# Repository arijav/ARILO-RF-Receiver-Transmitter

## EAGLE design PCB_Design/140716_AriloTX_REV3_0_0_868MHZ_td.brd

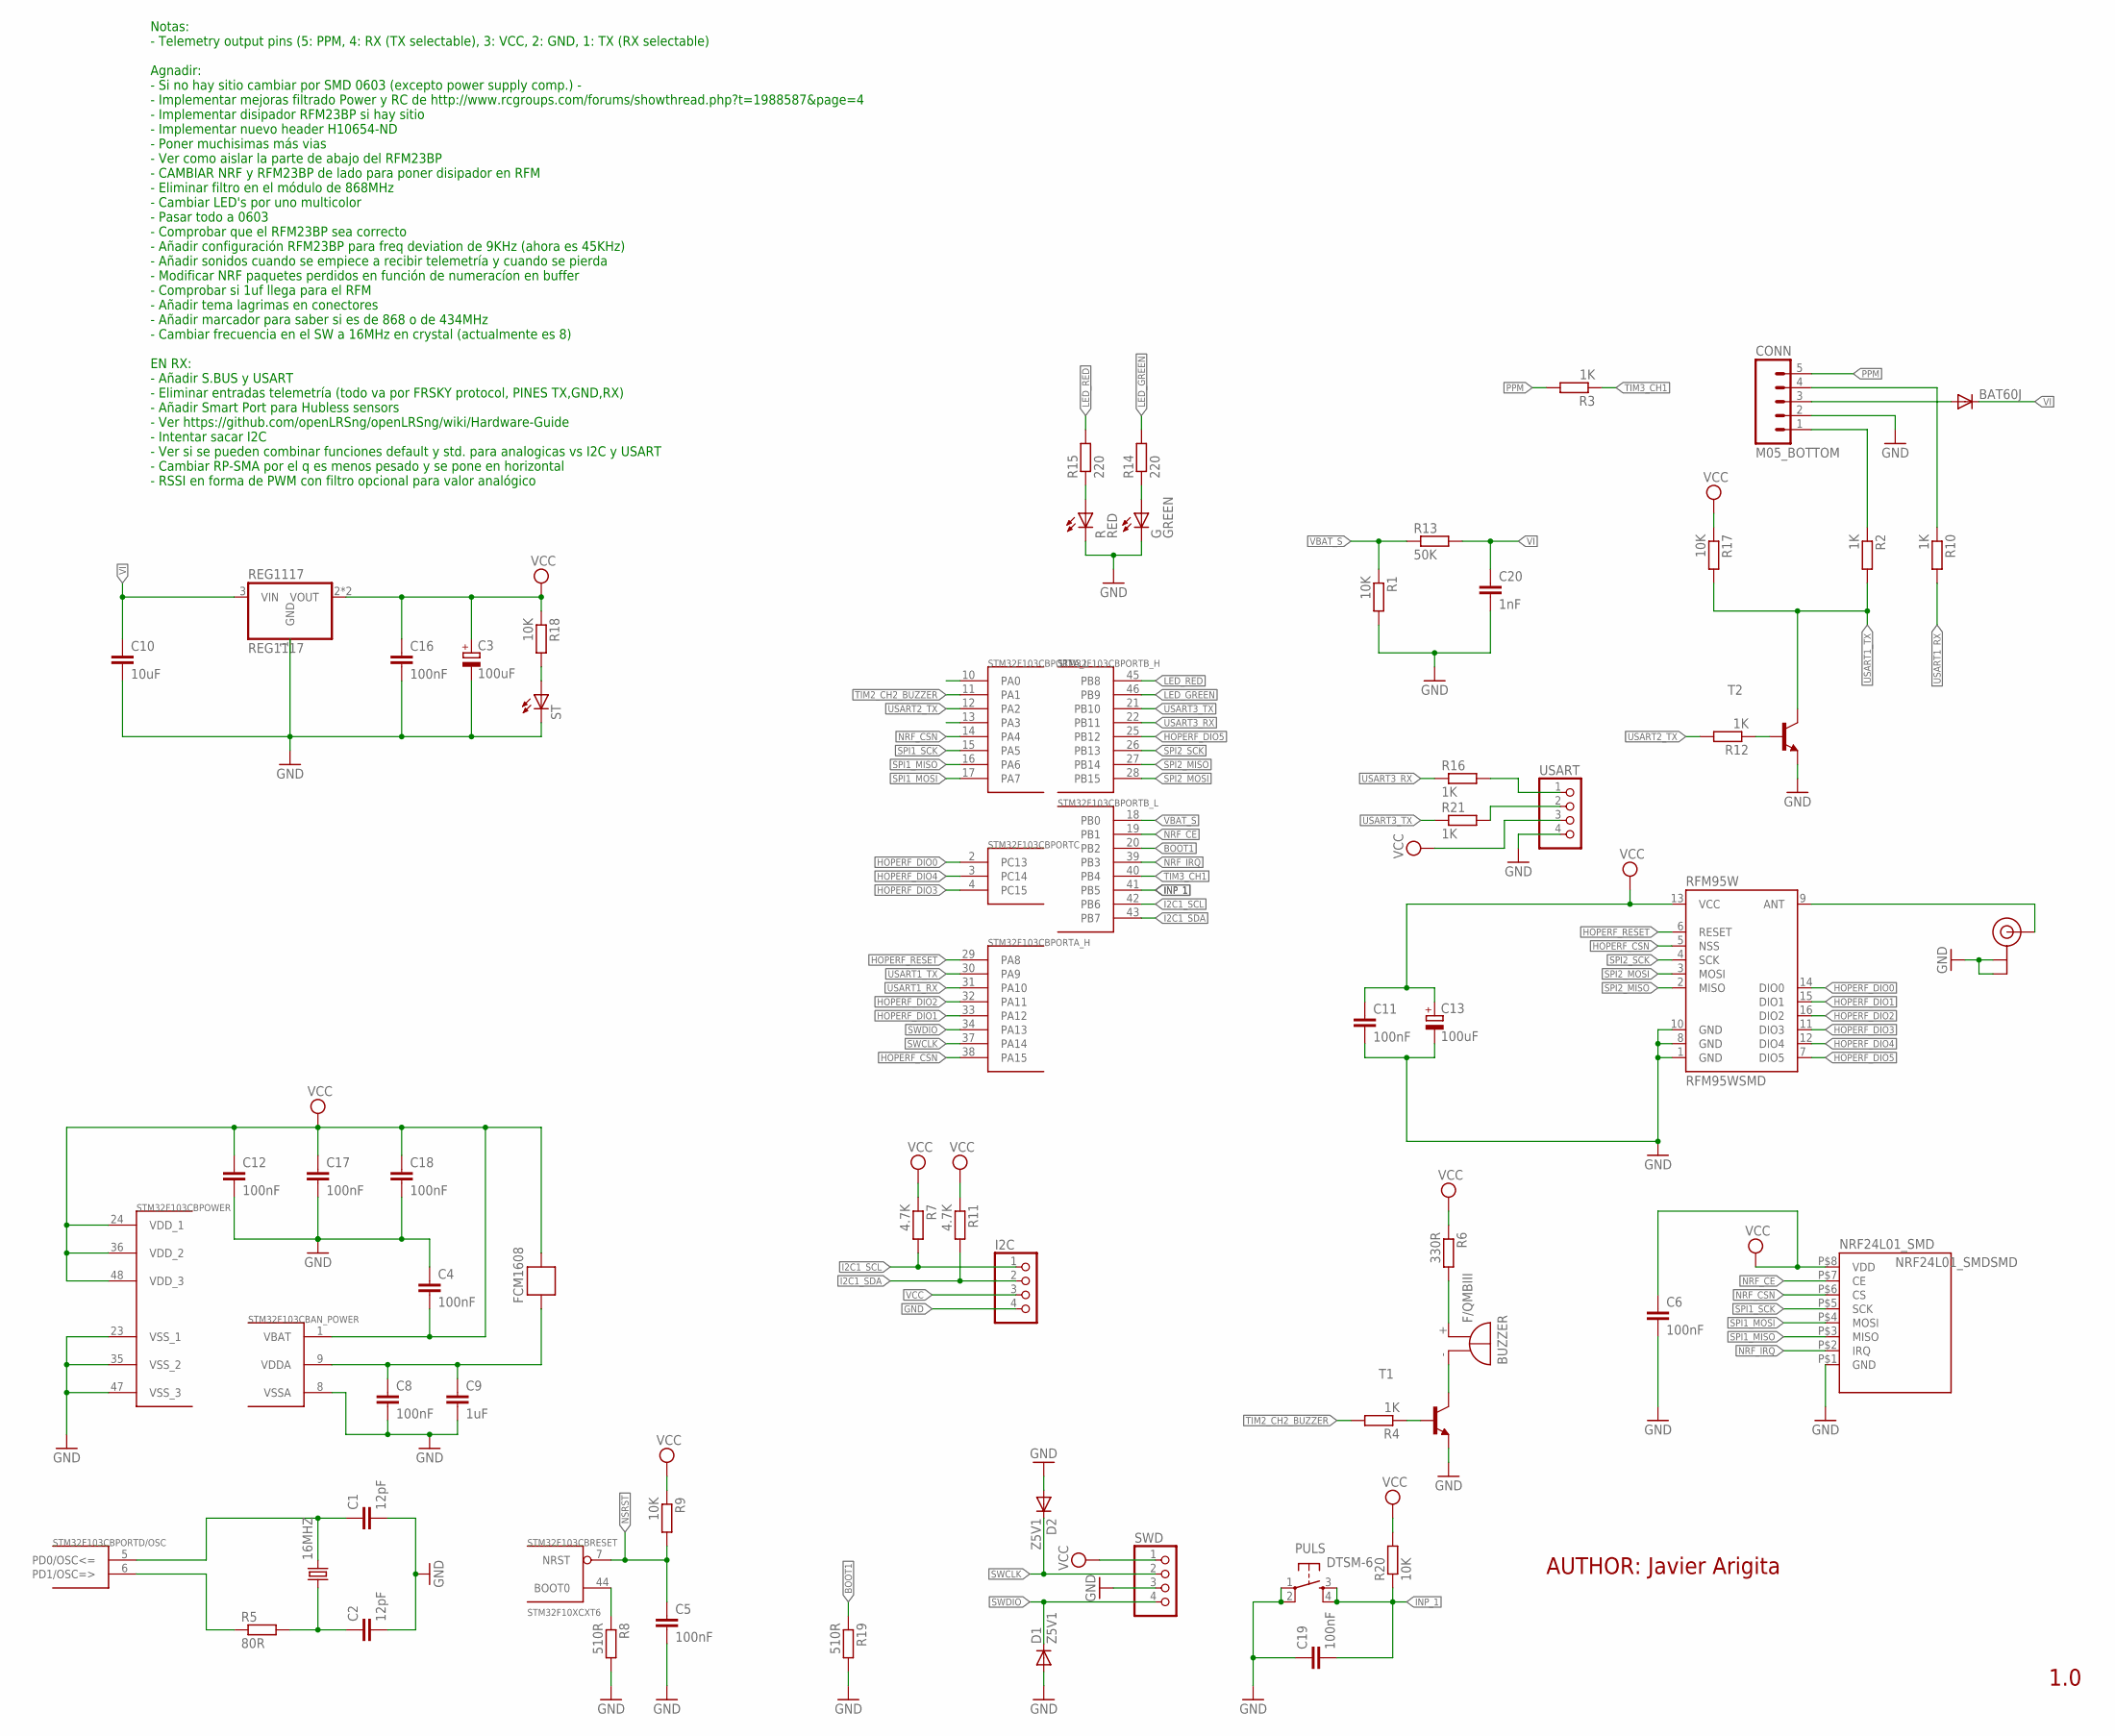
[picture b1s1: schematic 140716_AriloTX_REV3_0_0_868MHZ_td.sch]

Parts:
16MHZ: CRYSTAL5X3; CRYSTAL-SMD-5X3
BAT60J: DIODE-SOD323-R; SOD323-R
BUZZER: F/QMBIII
C1, C2: 12pF; C0603
C3, C13: 100uF; SMC_B
C4, C5, C6, C8, C11, C12, C16, C17, C18, C19: 100nF; C0603
C9: 1uF; C0603
C10: 10uF; C3216
C20: 1nF; C0603
CONN: M05_BOTTOM
D1, D2: Z5V1; SOD323-R
FCM1608: FERRITE-BEAD; R0603
G: GREEN; CHIP-LED0603
I2C: PINHD-1X4; 1X04
NRF24L01_SMD: NRF24L01_SMDSMD; NRF24L01_SMD
PULS: DTSM-6
R: RED; CHIP-LED0603
R1, R9, R17, R18, R20: 10K; R0603
R2, R3, R4, R10, R12, R16, R21: 1K; R0603
R5: 80R; R0603
R6: 330R; R0603
R7, R11: 4.7K; R0603
R8, R19: 510R; R0603
R13: 50K; R0603
R14, R15: 220; R0603
REG1117: REG1117; SOT223
RFM95W: RFM95WSMD; MISIEK_RFM95W_SMD
ST: LEDCHIP-LED0603; CHIP-LED0603
STM32F103CB: STM32F10XCXT6; TQFP48
SWD: PINHD-1X4; 1X04
T1, T2: BC848-NPN-SOT23-BEC; SOT23-BEC
U.FL: U.FL
USART: PINHD-1X4; 1X04

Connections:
BOOT1: R19.1, STM32F103CB.20 (PB2)
GND: C1.2, C2.2, C3.-, C4.1, C5.2, C6.2, C8.2, C9.2, C10.2, C11.2, C12.2, C13.-, C16.2, C17.2, C18.2, C19.1, C20.2, CONN.2, D1.A, D2.A, G.C, I2C.4, NRF24L01_SMD.P$1 (GND), PULS.1, PULS.2, R.C, R1.2, R8.2, R19.2, REG1117.1 (GND), RFM95W.1 (GND), RFM95W.8 (GND), RFM95W.10 (GND), ST.C, STM32F103CB.8 (VSSA), STM32F103CB.23 (VSS_1), STM32F103CB.35 (VSS_2), STM32F103CB.47 (VSS_3), SWD.3, T1.E, T2.E, U.FL.P$1 (GND), U.FL.P$2 (GND), USART.4
HOPERF_CSN: RFM95W.5 (NSS), STM32F103CB.38 (PA15)
HOPERF_DIO0: RFM95W.14 (DIO0), STM32F103CB.2 (PC13)
HOPERF_DIO1: RFM95W.15 (DIO1), STM32F103CB.33 (PA12)
HOPERF_DIO2: RFM95W.16 (DIO2), STM32F103CB.32 (PA11)
HOPERF_DIO3: RFM95W.11 (DIO3), STM32F103CB.4 (PC15)
HOPERF_DIO4: RFM95W.12 (DIO4), STM32F103CB.3 (PC14)
HOPERF_DIO5: RFM95W.7 (DIO5), STM32F103CB.25 (PB12)
HOPERF_RESET: RFM95W.6 (RESET), STM32F103CB.29 (PA8)
I2C1_SCL: I2C.1, R7.2, STM32F103CB.42 (PB6)
I2C1_SDA: I2C.2, R11.2, STM32F103CB.43 (PB7)
INP_1: C19.2, PULS.3, PULS.4, R20.1, STM32F103CB.41 (PB5)
LED_GREEN: R14.2, STM32F103CB.46 (PB9)
LED_RED: R15.2, STM32F103CB.45 (PB8)
unnamed: 16MHZ.3 (2), C1.1, STM32F103CB.5 (PD0/OSC<=)
unnamed: R5.1, STM32F103CB.6 (PD1/OSC=>)
unnamed: 16MHZ.1, C2.1, R5.2
unnamed: R8.1, STM32F103CB.44 (BOOT0)
unnamed: R12.1, T2.B
unnamed: CONN.1, R2.1
unnamed: R.A, R15.1
unnamed: G.A, R14.1
unnamed: CONN.4, R10.1
unnamed: R18.2, ST.A
unnamed: RFM95W.9 (ANT), U.FL.P$3 (SIGNAL)
unnamed: R16.2, USART.1
unnamed: R21.2, USART.2
unnamed: BAT60J.A, CONN.3
unnamed: BUZZER.+ (-), R6.2
unnamed: C8.1, C9.1, FCM1608.2, STM32F103CB.9 (VDDA)
unnamed: R4.1, T1.B
unnamed: BUZZER.- (+), T1.C
NRF_CE: NRF24L01_SMD.P$7 (CE), STM32F103CB.19 (PB1)
NRF_CSN: NRF24L01_SMD.P$6 (CS), STM32F103CB.14 (PA4)
NRF_IRQ: NRF24L01_SMD.P$2 (IRQ), STM32F103CB.39 (PB3)
NSRST: C5.1, R9.2, STM32F103CB.7 (NRST)
PPM: CONN.5, R3.2
SPI1_MISO: NRF24L01_SMD.P$3 (MISO), STM32F103CB.16 (PA6)
SPI1_MOSI: NRF24L01_SMD.P$4 (MOSI), STM32F103CB.17 (PA7)
SPI1_SCK: NRF24L01_SMD.P$5 (SCK), STM32F103CB.15 (PA5)
SPI2_MISO: RFM95W.2 (MISO), STM32F103CB.27 (PB14)
SPI2_MOSI: RFM95W.3 (MOSI), STM32F103CB.28 (PB15)
SPI2_SCK: RFM95W.4 (SCK), STM32F103CB.26 (PB13)
SWCLK: D2.C, STM32F103CB.37 (PA14), SWD.2
SWDIO: D1.C, STM32F103CB.34 (PA13), SWD.4
TIM2_CH2_BUZZER: R4.2, STM32F103CB.11 (PA1)
TIM3_CH1: R3.1, STM32F103CB.40 (PB4)
USART1_RX: R10.2, STM32F103CB.31 (PA10)
USART1_TX: R2.2, R17.2, STM32F103CB.30 (PA9), T2.C
USART2_TX: R12.2, STM32F103CB.12 (PA2)
USART3_RX: R16.1, STM32F103CB.22 (PB11)
USART3_TX: R21.1, STM32F103CB.21 (PB10)
VBAT_S: R1.1, R13.1, STM32F103CB.18 (PB0)
VCC: C3.+, C4.2, C6.1, C11.1, C12.1, C13.+, C16.1, C17.1, C18.1, FCM1608.1, I2C.3, NRF24L01_SMD.P$8 (VDD), R6.1, R7.1, R9.1, R11.1, R17.1, R18.1, R20.2, REG1117.2 (VOUT), REG1117.4 (VOUT), RFM95W.13 (VCC), STM32F103CB.1 (VBAT), STM32F103CB.24 (VDD_1), STM32F103CB.36 (VDD_2), STM32F103CB.48 (VDD_3), SWD.1, USART.3
VI: BAT60J.C, C10.1, C20.1, R13.2, REG1117.3 (VIN)

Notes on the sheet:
AUTHOR: Javier Arigita
1.0
Notas: - Telemetry output pins (5: PPM, 4: RX (TX selectable), 3: VCC, 2: GND, 1: TX (RX selectable) Agnadir: - Si no hay sitio cambiar por SMD 0603 (excepto power supply comp.) - - Implementar mejoras filtrado Power y RC de http://www.rcgroups.com/forums/showthread.php?t=1988587&page=4 - Implement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

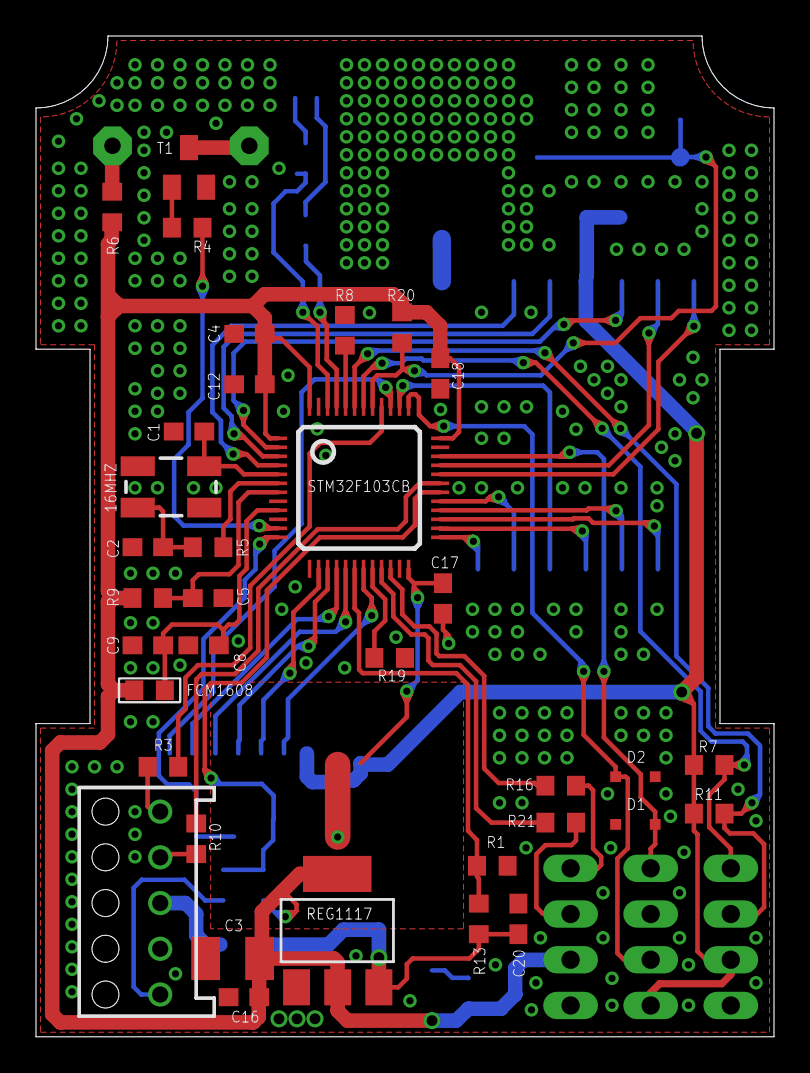
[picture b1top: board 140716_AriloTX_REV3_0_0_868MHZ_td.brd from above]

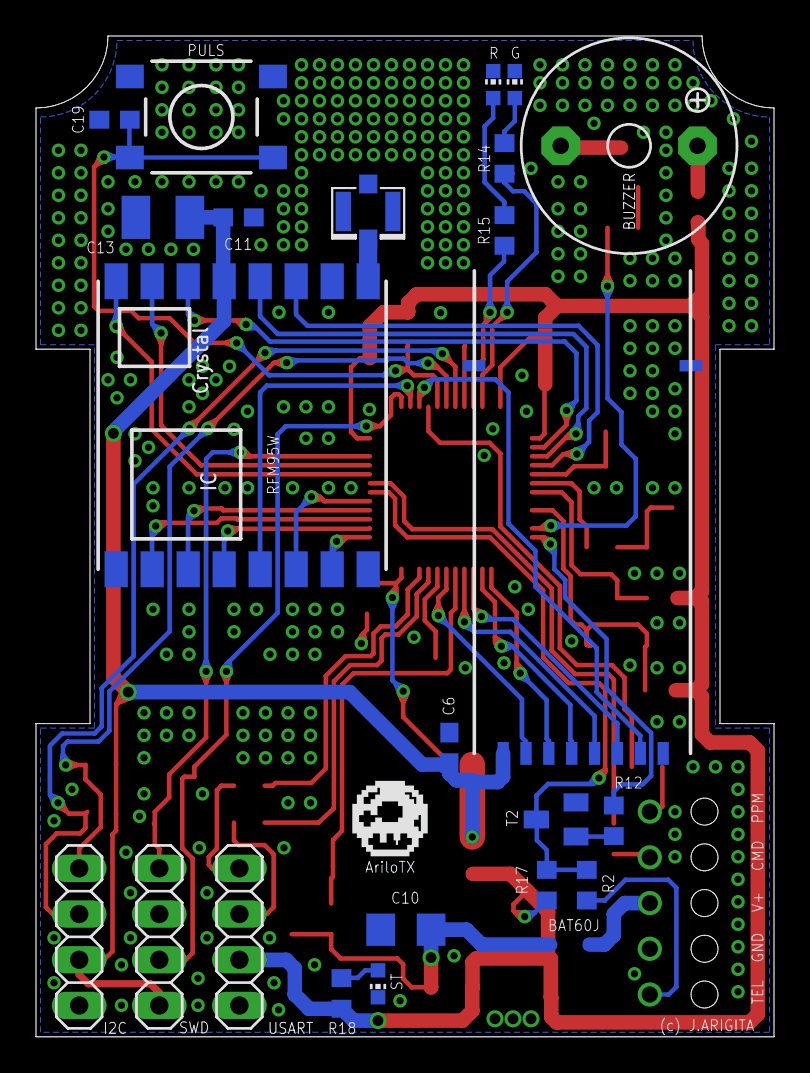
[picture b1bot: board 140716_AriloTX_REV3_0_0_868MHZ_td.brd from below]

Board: 2 copper layers, 41.0 x 55.6 mm, 59 parts (24 on the bottom side), 56 nets.

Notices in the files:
parts and their libraries:
SparkFun-FreqCtrl: Licensing: CC v3.0 Share-Alike You are welcome to use this library for commercial purposes.
